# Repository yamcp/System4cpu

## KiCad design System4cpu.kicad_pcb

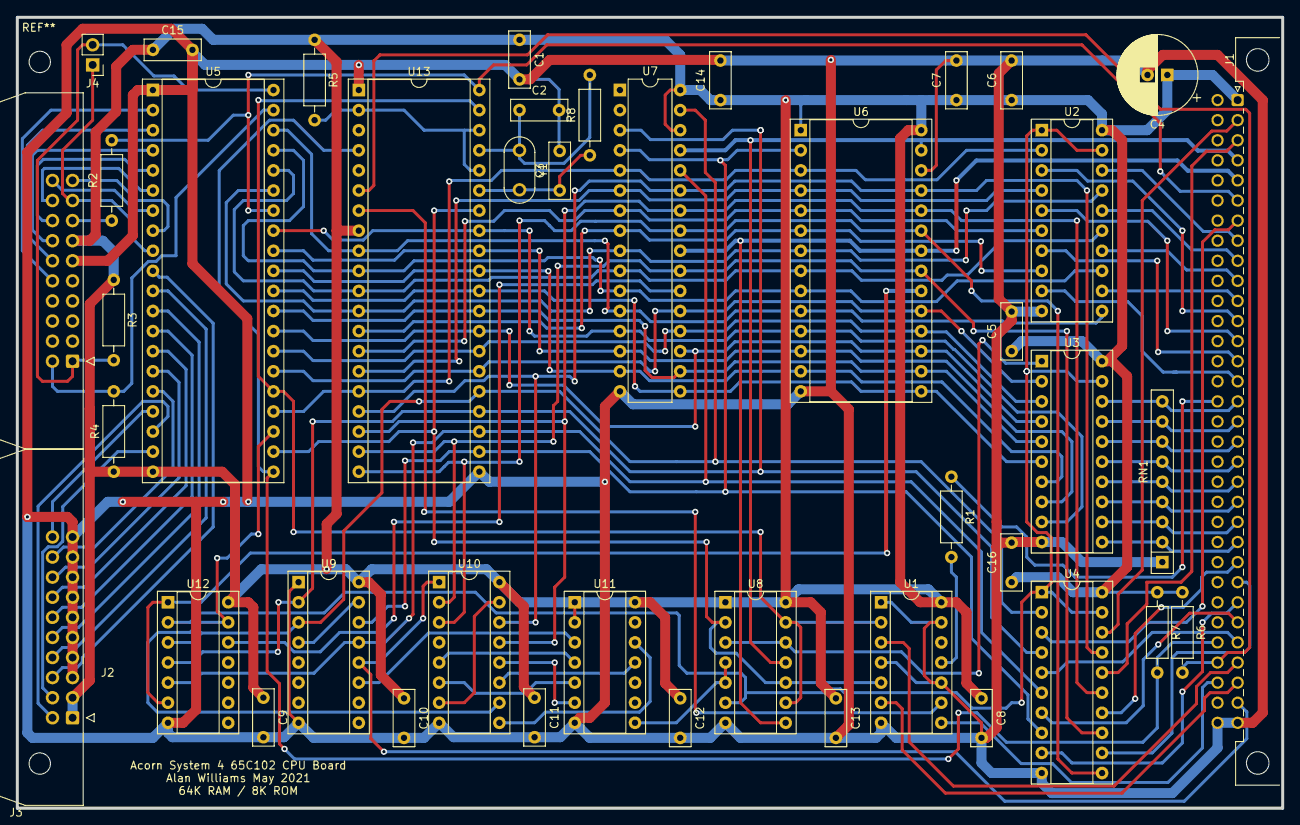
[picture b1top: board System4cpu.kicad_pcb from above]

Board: 2 copper layers, 160.0 x 100.0 mm, 43 parts (0 on the bottom side), 102 nets.

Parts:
C1, C5, C6, C7, C8, C9, C10, C11, C12, C13, C14, C15, C16: 0.1; C_Rect_L7.0mm_W2.5mm_P5.00mm
C2, C3: 33pf; C_Rect_L7.0mm_W2.5mm_P5.00mm
C4: 500uF16v; CP_Radial_D10.0mm_P2.50mm
J1: din41612_C64AB; DIN41612_B_2x32_Male_Horizontal_THT
J2: Keyboard; IDC-Header_2x10_P2.54mm_Latch_Horizontal
J3: USERport; IDC-Header_2x10_P2.54mm_Latch_Horizontal
J4: Conn_01x02; PinHeader_1x02_P2.54mm_Vertical
R1: 68R; R_Axial_DIN0207_L6.3mm_D2.5mm_P10.16mm_Horizontal
R2: 100; R_Axial_DIN0207_L6.3mm_D2.5mm_P10.16mm_Horizontal
R3, R4, R6: 4K7; R_Axial_DIN0207_L6.3mm_D2.5mm_P10.16mm_Horizontal
R5: 10K; R_Axial_DIN0207_L6.3mm_D2.5mm_P10.16mm_Horizontal
R7: 4k7; R_Axial_DIN0207_L6.3mm_D2.5mm_P10.16mm_Horizontal
R8: 4M7; R_Axial_DIN0207_L6.3mm_D2.5mm_P10.16mm_Horizontal
RN1: 2k2; R_Array_SIP9
U1: 74LS125; DIP-14_W7.62mm_Socket
U2, U4: 74LS244; DIP-20_W7.62mm_Socket
U3: 74LS245; DIP-20_W7.62mm_Socket
U5: 6522; DIP-40_W15.24mm_Socket
U6: AT28C64B; DIP-28_W15.24mm_Socket
U7: W24512A 64K SRAM; DIP-32_W7.62mm
U8: 74LS00; DIP-14_W7.62mm_Socket
U9, U10: 74LS139; DIP-16_W7.62mm_Socket
U11: 74LS30; DIP-14_W7.62mm_Socket
U12: 74LS11; DIP-14_W7.62mm_Socket
U13: 65C102; DIP-40_W15.24mm_Socket
Y1: 4MHz; Resonator-2Pin_W8.0mm_H3.5mm

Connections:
/eurocard/B4MHZ: J1.b16, R1.1
/eurocard/BA0: J1.a15, U2.9
/eurocard/BA1: J1.a14, U2.7
/eurocard/BA2: J1.a13, U2.5
/eurocard/BA3: J1.a12, U2.3
/eurocard/BA4: J1.a11, U2.12
/eurocard/BA5: J1.a10, U2.14
/eurocard/BA6: J1.a9, U2.16
/eurocard/BA7: J1.a8, U2.18
/eurocard/BA8: J1.a7, U4.3
/eurocard/BA9: J1.a28, U4.5
/eurocard/BA10: J1.a27, U4.7
/eurocard/BA11: J1.a26, U4.9
/eurocard/BA12: J1.a25, U4.12
/eurocard/BA13: J1.a24, U4.14
/eurocard/BA14: J1.a3, U4.16
/eurocard/BA15: J1.a2, U4.18
/eurocard/BD0: J1.a23, RN1.2, U3.11
/eurocard/BD1: J1.a22, RN1.3, U3.12
/eurocard/BD2: J1.a21, RN1.4, U3.13
/eurocard/BD3: J1.a20, RN1.5, U3.14
/eurocard/BD4: J1.a19, RN1.6, U3.15
/eurocard/BD5: J1.a18, RN1.7, U3.16
/eurocard/BD6: J1.a17, RN1.8, U3.17
/eurocard/BD7: J1.a16, RN1.9, U3.18
/eurocard/BPHI2: J1.a29, U1.3
/eurocard/BRNW: J1.a30, U1.6
/eurocard/BSYNC: J1.b30, U1.8
A0: U2.11, U5.38, U6.10, U7.12, U13.9
A1: U2.13, U5.37, U6.9, U7.11, U13.10
A2: U2.15, U5.36, U6.8, U7.10, U13.11
A3: U2.17, U5.35, U6.7, U7.9, U13.12
A4: U2.8, U6.6, U7.8, U13.13
A5: U2.6, U6.5, U7.7, U13.14
A6: U2.4, U6.4, U7.6, U13.15
A7: U2.2, U5.24, U6.3, U7.5, U13.16
A8: U4.17, U6.25, U7.27, U10.14, U13.17
A9: U4.15, U6.24, U7.26, U10.13, U13.18
A10: U4.13, U6.21, U7.23, U10.2, U13.19
A11: U4.11, U6.23, U7.25, U10.3, U13.20
A12: U4.8, U6.2, U7.4, U9.14, U13.22
A13: U4.6, U7.28, U9.13, U12.5, U13.23
A14: U4.4, U7.3, U9.2, U12.4, U13.24
A15: U4.2, U7.31, U9.3, U12.3, U13.25
CA1: J2.1, J4.2, R3.2, U5.40
CA2: J2.2, R4.2, U5.39
CB1: J3.2, U5.18
CB2: J3.4, U5.19
D0: U3.9, U5.33, U6.11, U7.13, U13.33
D1: U3.8, U5.32, U6.12, U7.14, U13.32
D2: U3.7, U5.31, U6.13, U7.15, U13.31
D3: U3.6, U5.30, U6.15, U7.17, U13.30
D4: U3.5, U5.29, U6.16, U7.18, U13.29
D5: U3.4, U5.28, U6.17, U7.19, U13.28
D6: U3.3, U5.27, U6.18, U7.20, U13.27
D7: U3.2, U5.26, U6.19, U7.21, U13.26
GND: C1.2, C2.2, C3.2, C4.2, C5.2, C6.2, C7.2, C8.2, C9.2, C10.2, C11.2, C12.2, C13.2, C14.2, C15.2, C16.2, J1.a32, J1.b32, J2.11, J3.5, J3.7, J3.9, J3.11, J3.13, J3.15, J3.17, J3.19, RN1.1, U1.1, U1.4, U1.7, U1.10, U1.13, U2.10, U3.10, U4.10, U5.1, U6.14, U6.26, U7.16, U8.7, U9.1, U9.8, U10.8, U11.7, U12.7, U13.1, U13.21
NBLK0: J1.a31, U9.12, U10.1
NBLK1: U9.11, U11.3
NBLKEF: U6.20, U12.1, U12.6
NIRQ: J1.b28, R7.2, U5.21, U13.4
NMI: J1.b29, R6.2, U13.6
NOB: U2.1, U2.19, U3.19, U4.1, U4.19, U8.6, U12.2
NRAMCS: U7.22, U12.12
NRDS: J1.a5, U6.22, U7.24, U8.8
NRST: J1.a6, R2.2, U5.34, U13.40
NVIA: U5.23, U10.10, U12.13
NWDS: J1.a4, U6.27, U7.29, U8.11
unnamed: C2.1, R8.2, U13.37, Y1.1
unnamed: C3.1, R8.1, U13.35, Y1.2
unnamed: J2.15, R2.1
unnamed: R1.2, U1.11
unnamed: R5.2, U13.2, U13.36, U13.38
unnamed: U9.4, U9.15
unnamed: U10.5, U11.4
unnamed: U10.6, U11.5
unnamed: U10.9, U11.12
unnamed: U10.11, U11.11
unnamed: U10.12, U11.6
unnamed: U10.7, U10.15
unnamed: U8.4, U8.5, U11.8
PA0: J2.10, U5.2
PA1: J2.12, U5.3
PA2: J2.14, U5.4
PA3: J2.16, U5.5
PA4: J2.18, U5.6
PA5: J2.20, U5.7
PA6: J2.19, U5.8
PA7: J2.17, J4.1, U5.9
PB0: J3.6, U5.10
PB1: J3.8, U5.11
PB2: J3.10, U5.12
PB3: J3.12, U5.13
PB4: J3.14, U5.14
PB5: J3.16, U5.15
PB6: J3.18, U5.16
PB7: J3.20, U5.17
PHI2: U1.2, U5.25, U8.9, U8.13, U13.39
RNW: U1.5, U5.22, U8.2, U8.10, U13.34
SYNC: U1.9, U13.7
VCC: C1.1, C4.1, C5.1, C6.1, C7.1, C8.1, C9.1, C10.1, C11.1, C12.1, C13.1, C14.1, C15.1, C16.1, J1.a1, J2.13, J3.1, J3.3, R3.1, R4.1, R5.1, R6.1, R7.1, U1.14, U2.20, U3.20, U4.20, U5.20, U6.1, U6.28, U7.30, U7.32, U8.1, U8.14, U9.16, U10.16, U11.1, U11.2, U11.14, U12.14, U13.8
WNR: U3.1, U8.3, U8.12
